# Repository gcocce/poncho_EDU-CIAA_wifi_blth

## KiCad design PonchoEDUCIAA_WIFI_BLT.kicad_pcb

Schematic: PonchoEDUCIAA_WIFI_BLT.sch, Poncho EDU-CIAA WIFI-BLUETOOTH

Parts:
C1: 0,1uF; C_0603_HandSoldering; Mouser# 581-02016D104KAT2A; Digikey# 478-5266-1-ND
C2: 10uF; C_0603_HandSoldering; Mouser# 81-GRM219R60J106KE9D; Digikey# 490-3340-1-ND
C3: 1nF; C_0603_HandSoldering; Mouser# 81-GRM1555C1H101JA1D; Digikey# 490-5922-1-ND
C4: 0,1nF; C_0603_HandSoldering; Mouser# 81-GRM1555C1H100JA1D; Digikey# 490-5921-1-ND
C5: 1nF; C_0603_HandSoldering; Mouser# 581-0201ZA101JAT2A; Digikey# 478-1026-1-ND
D1: LED_Rojo; LED_0402; Mouser# 645-550-0504F; Digikey# 350-1608-ND
D2: LED_Verde; LED_0402; Mouser# 645-561-2201-050F; Digikey# 350-2814-ND
D3: LED_Amarillo; LED_0402; Mouser# 645-550-0804F; Digikey# 350-1615-ND
F1, F2, F3: FIDUCIAL; Fiducial_1mm
J1: UART; CON_PALETA_3; Mouser# 538-22-27-2031; Digikey# WM4112-ND
R1, R4, R5: 402; R_0805_HandSoldering; Mouser# 603-RC0805FR-07402RL; Digikey# 311-402CRCT-ND
R2: 10k; R_0805_HandSoldering; Mouser# 667-ERA-6AEB103V; Digikey# P10KDACT-ND
R3, R6: 470; R_0805_HandSoldering; Mouser# 603-RC0805FR-07470RL; Digikey# 311-470CRCT-ND
R7, R8: 5k; R_0805_HandSoldering; Mouser# 71-CRCW0805-5K; Digikey# CRCW08055K00FKTA-ND
SW1: Reset; SW_PUSH_6mm; Mouser# 611-D6C90F1LFS; Digikey# 401-1969-ND
SW2: Boot; SW_Micro_SPST; Mouser# 611-JS202011CQN; Digikey# 401-2001-ND
U1: ESP32-WROOM; Mouser# 485-3320; Digikey# 1528-1801-ND
XA1: Conn_Poncho2P_2x_20x2; Conn_Poncho_Derecha; Mouser# 855-M50-3501042; Digikey# 952-1386-ND

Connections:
+3V3: C1.2, C2.2, R1.2, R2.1, R7.1, U1.2 (3V3), XA1.1 (+3.3V)
GND: C1.1, C2.1, C3.2, C4.2, C5.1, D1.1 (K), D2.1 (K), D3.1 (K), J1.3, R8.1, SW1.1, SW2.2 (B), U1.1 (GND), U1.15 (GND), U1.38 (GND), U1.39 (GND-PAD), XA1.4 (GND), XA1.20 (GND), XA1.22 (GND), XA1.24 (GND), XA1.26 (GND), XA1.28 (GND), XA1.30 (GND), XA1.32 (GND), XA1.38 (GND), XA1.40 (GND)
unnamed: C3.1, R3.1, SW1.2
unnamed: C4.1, R2.2, R3.2, U1.3 (EN)
unnamed: C5.2, R6.1, SW2.3 (C)
unnamed: D1.2 (A), R1.1
unnamed: D2.2 (A), R5.2
unnamed: D3.2 (A), R4.2
unnamed: J1.1, R5.1, U1.35 (TXD0), XA1.23 (rs232RXD)
unnamed: J1.2, R4.1, U1.34 (RXD0), XA1.25 (rs232TXD)
unnamed: R6.2, R7.2, U1.25 (IO0)
unnamed: R8.2, U1.24 (IO2)

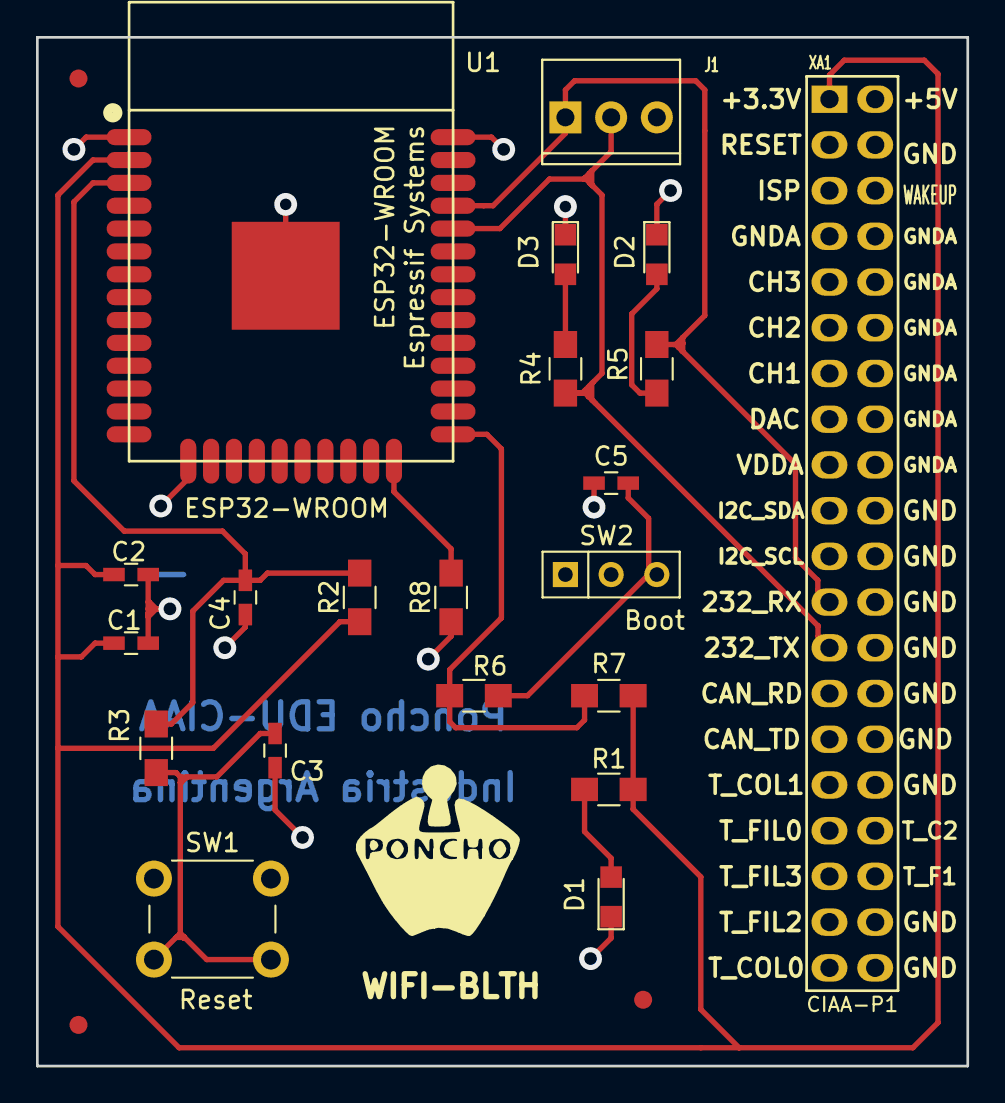
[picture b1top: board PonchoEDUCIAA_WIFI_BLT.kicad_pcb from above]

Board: 2 copper layers, 51.7 x 57.2 mm, 25 parts (0 on the bottom side), 12 nets.

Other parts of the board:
G1: WIFI-BLTH; Logo_Poncho

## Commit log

2017-05-12 Se agrega datasheet del modulo esp-wroom-32
2017-05-12 Modificamos estructura de directorios
2017-05-12 Agregamos leds al esquematico para la alimentación y la comunicación UART
2017-05-16 Agregado de circuitos al esquematico
2017-05-16 Ultimos agregados al esquematico
2017-05-25 Se agregan switches al esquematico
2017-05-25 Se agregan los footprints
2017-05-26 Agregamos la vista 3d del componente ESP-WROOM-32
2017-05-30 Se soluciona problema al importar netlist al pcbnew
2017-05-30 Se distribuyen los componentes en el PCB
2017-06-01 Se agregan modelos 3d al proyecto y datashets de algunos componentes
2017-06-08 reorganizacion de directorios
2017-06-09 Se cargan todos los campos de los componentes del esquematico y se exporta el bom y se generan documentos
2017-06-24 Se agrega resistencia sugerida por revisor
2017-06-24 Se incorpora el nuevo netlist al pcb
2017-07-02 Se realizan cambios sugeridos por revisor Diego Bregni: rotulos, unificar resistencias 805, mejora prolijidad de conexiones, se agrega codigo mouser, revisiones y proyecto en carpeta doc.
2017-07-02 Agregamos los cambios realizados al proyecto
2017-07-08 Revision del proyecto
2017-07-10 Primer ruteo tentativo
2017-07-12 Rediseño de las conexiones del pcb
2017-07-13 Se corrigen detalles en el pcb y se generan imagenes de la vista 3d
2017-07-13 Se exportaron los componentes a una libreria, se borraron las librerias del proyecto y se corrigieron los nombres de los directorios.
2017-07-13 Se generan los archivos gerber y se actualiza el listado de materiales
2017-07-13 Se generan los listados de materiales y se genera el impreso del esquematico
2017-07-14 Se actualiza el proyecto
2017-07-14 Se genera el presupuesto con kicost
2017-08-02 Se cambian los leds, sus datasheets y el footprint para unformizar en 0805 smd
2017-08-10 Se rehace el placement y el ruteo, se agregan descripciones y zona de cobre.
2017-08-10 Se mejora el pcb y la vist 3d. Se actualizan los costos con kicost. Se agrega tutorial FreeRouting
